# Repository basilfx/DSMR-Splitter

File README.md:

# DSMR Splitter
Active port expander for the P1 port on a Dutch Smart Meter (DSMR).

## Introduction
This is an active port expander for DSMR 5.0. Contrary to simple splitting
cables, this exapander buffers telegrams, and provides a dedicated port to
connected devices.

### Advantages
This design solves two (potential) issues compared to other splitters:

* Some port splitters have a primary and a secondary port. Only the primary
  port has the data-request line connected to the DSMR. This means that the
  secondary port cannot request telegrams on its own and depends on the device
  connected to the master port.
* A device connected to the secondary port could receive out-of-sync, if it
  depends on the data-request line. This could lead to incomplete/corrupt
  telegrams.

See [this](docs/Problem-statement.md) for more information.

## Features
* 3-port splitter.
* DSMR 5.0.
* No external power supply needed.

The splitter provides galvanic isolation between ports, if the 5 V is not used.
To read more on how this was achieved, see [this](docs/Isolation.md).

Furthemore, it requires a DSMR 5.0 meter because it provides 5 V power. Do note
that the power (5 V, 250 mA) provided by the DSMR has to be shared among all
readers, and the splitter itself requires ~50 mA.

Older DSMR versions can be supported by changing the firmware and providing 5 V
externally.

## Contents
* The `3d/` folder contains a 3D-printable design for an enclosure.
* The `firmware/` folder contains the RIOT-OS firmware used for the
  microcontroller.
* The `pcb/` folder contains the Kicad schema and board design.
* The `tools/` folder contains additional tools, such as a DSMR simulator.

## License
The work in this repository is covered by CC BY-NC-SA 4.0. See the `LICENSE.md`
file for more information.

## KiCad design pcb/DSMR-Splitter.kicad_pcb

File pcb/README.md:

# DSMR Splitter

## Features
* ARM Cortex M4 CPU with 1 MiB of flash and 256 KiB of RAM.
* 3 isolated output ports.
* Status LED.

## Board

## Schema
You can find the schema [here](DSMR-Splitter.pdf).

## BoM
The (interactive) BoM can be found [here](https://basilfx.github.io/DSMR-Splitter/pcb/BoM/ibom.html).

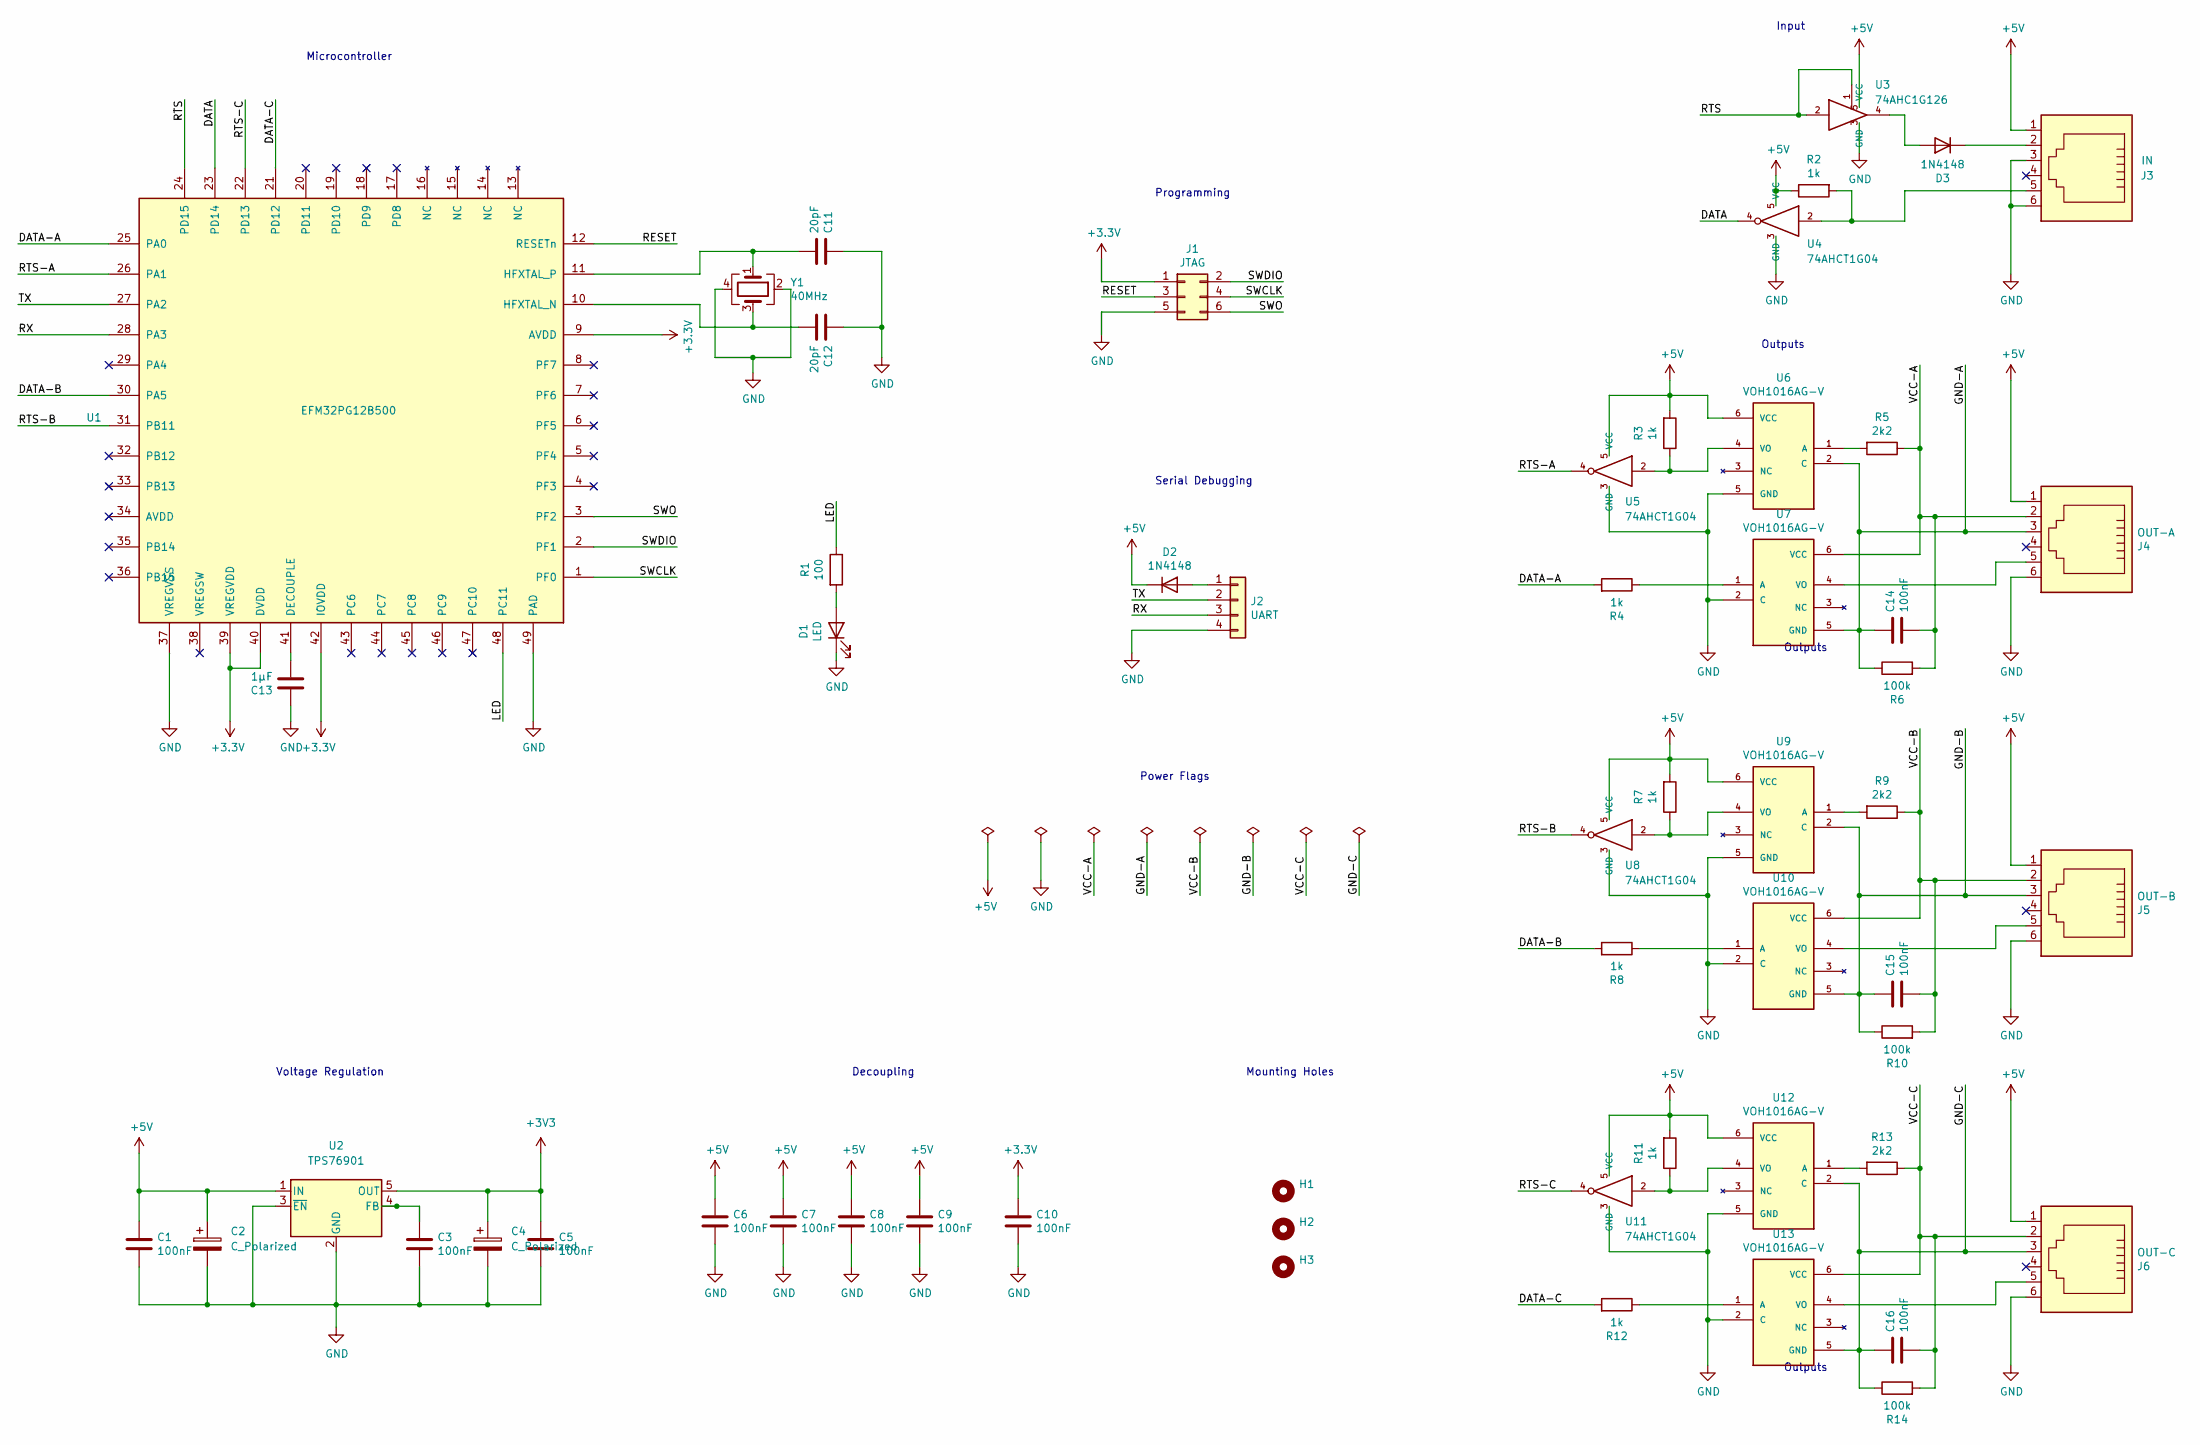
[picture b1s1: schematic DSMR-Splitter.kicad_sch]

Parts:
C1, C3, C5, C6, C7, C8, C9, C10, C14, C15, C16: 100nF; C_0603_1608Metric
C2, C4: C_Polarized; CP_EIA-3216-12_Kemet-S
C11, C12: 20pF; C_0603_1608Metric
C13: 1µF; C_0603_1608Metric
D1: LED; LED_0603_1608Metric
D2, D3: 1N4148; D_0603_1608Metric
H1, H2, H3: MountingHole; MountingHole_2.2mm_M2
J1: JTAG; PinHeader_2x03_P1.27mm_Vertical
J2: UART; PinHeader_1x04_P1.27mm_Vertical
J3: IN; RJ12_Amphenol_54601
J4: OUT-A; RJ12_Amphenol_54601
J5: OUT-B; RJ12_Amphenol_54601
J6: OUT-C; RJ12_Amphenol_54601
R1: 100; R_0603_1608Metric
R2, R3, R4, R7, R8, R11, R12: 1k; R_0603_1608Metric
R5, R9, R13: 2k2; R_0603_1608Metric
R6, R10, R14: 100k; R_0603_1608Metric
U1: EFM32PG12B500; QFN-48-1EP_7x7mm_P0.5mm_EP5.3x5.3mm
U2: TPS76901; SOT-23-5
U3: 74AHC1G126; SOT-23-5
U4, U5, U8, U11: 74AHCT1G04; SOT-23-5
U6, U7, U9, U10, U12, U13: VOH1016AG-V; SMDIP-6_W7.62mm; PARTREV 1.1
Y1: 40MHz; Crystal_SMD_2016-4Pin_2.0x1.6mm

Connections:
+5V: C1.1, C2.1, C6.1, C7.1, C8.1, C9.1, D2.1 (K), J3.1, J4.1, J5.1, J6.1, R2.1, R3.2, R7.2, R11.2, U2.1 (IN), U3.5 (VCC), U4.5 (VCC), U5.5 (VCC), U6.6 (VCC), U8.5 (VCC), U9.6 (VCC), U11.5 (VCC), U12.6 (VCC)
/DATA: U1.23 (PD14), U4.4
/DATA-A: R4.2, U1.25 (PA0)
/DATA-B: R8.2, U1.30 (PA5)
/DATA-C: R12.2, U1.21 (PD12)
/GND-A: C14.1, J4.3, R6.1, U6.2 (C), U7.5 (GND)
/GND-B: C15.1, J5.3, R10.1, U9.2 (C), U10.5 (GND)
/GND-C: C16.1, J6.3, R14.1, U12.2 (C), U13.5 (GND)
/LED: R1.1, U1.48 (PC11)
/RESET: J1.3, U1.12 (RESETn)
/RTS: U1.24 (PD15), U3.1, U3.2
/RTS-A: U1.26 (PA1), U5.4
/RTS-B: U1.31 (PB11), U8.4
/RTS-C: U1.22 (PD13), U11.4
/RX: J2.3, U1.28 (PA3)
/SWCLK: J1.4, U1.1 (PF0)
/SWDIO: J1.2, U1.2 (PF1)
/SWO: J1.6, U1.3 (PF2)
/TX: J2.2, U1.27 (PA2)
/VCC-A: C14.2, J4.2, R5.1, R6.2, U7.6 (VCC)
/VCC-B: C15.2, J5.2, R9.1, R10.2, U10.6 (VCC)
/VCC-C: C16.2, J6.2, R13.1, R14.2, U13.6 (VCC)
GND: C1.2, C2.2, C3.2, C4.2, C5.2, C6.2, C7.2, C8.2, C9.2, C10.2, C11.1, C12.1, C13.1, D1.1 (K), J1.5, J2.4, J3.3, J3.6, J4.6, J5.6, J6.6, U1.37 (VREGVSS), U1.49 (PAD), U2.2 (GND), U2.3 (~EN), U3.3 (GND), U4.3 (GND), U5.3 (GND), U6.5 (GND), U7.2 (C), U8.3 (GND), U9.5 (GND), U10.2 (C), U11.3 (GND), U12.5 (GND), U13.2 (C), Y1.2, Y1.4
unnamed: C3.1, U2.4 (FB)
unnamed: C11.2, U1.11 (HFXTAL_P), Y1.1
unnamed: C12.2, U1.10 (HFXTAL_N), Y1.3
unnamed: C13.2, U1.41 (DECOUPLE)
unnamed: D1.2 (A), R1.2
unnamed: D2.2 (A), J2.1
unnamed: D3.1 (K), J3.2
unnamed: D3.2 (A), U3.4
unnamed: J3.5, R2.2, U4.2
unnamed: J4.5, U7.4 (VO)
unnamed: J5.5, U10.4 (VO)
unnamed: J6.5, U13.4 (VO)
unnamed: R3.1, U5.2, U6.4 (VO)
unnamed: R4.1, U7.1 (A)
unnamed: R5.2, U6.1 (A)
unnamed: R7.1, U8.2, U9.4 (VO)
unnamed: R8.1, U10.1 (A)
unnamed: R9.2, U9.1 (A)
unnamed: R11.1, U11.2, U12.4 (VO)
unnamed: R12.1, U13.1 (A)
unnamed: R13.2, U12.1 (A)

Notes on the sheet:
Decoupling
Microcontroller
Outputs
Input
Serial Debugging
Mounting Holes
Voltage Regulation
Programming
Power Flags

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
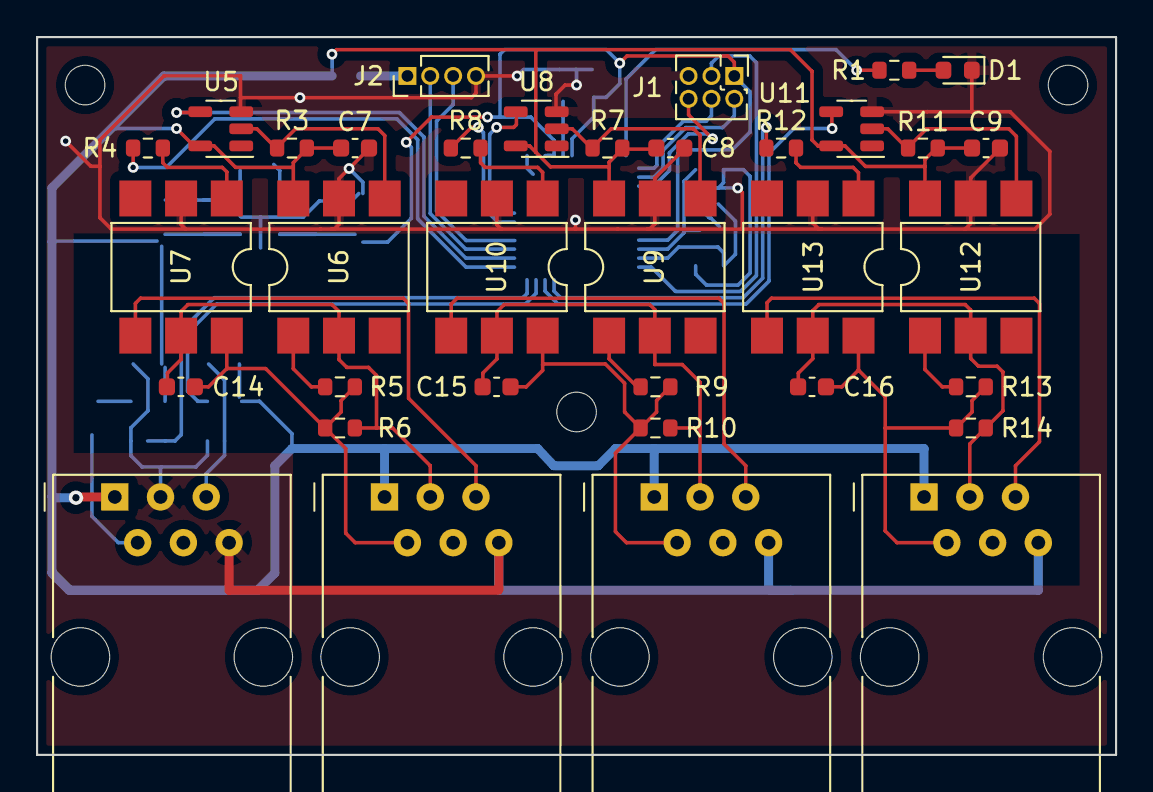
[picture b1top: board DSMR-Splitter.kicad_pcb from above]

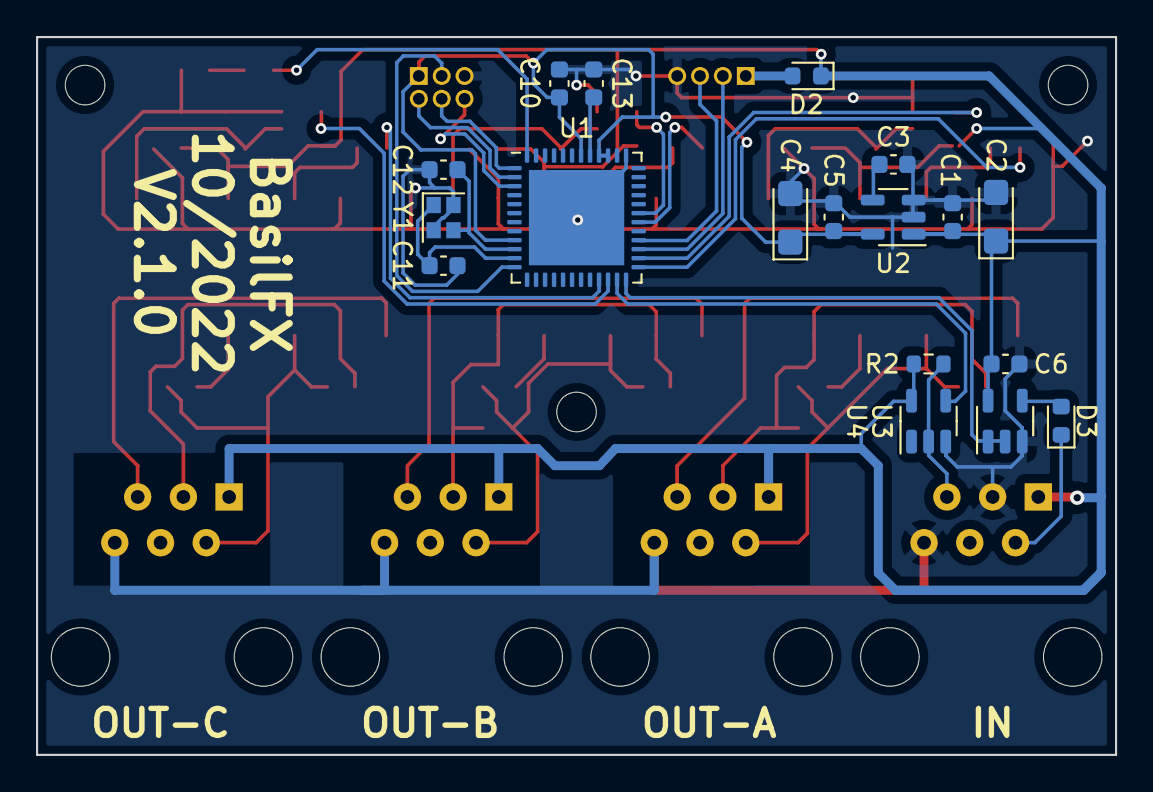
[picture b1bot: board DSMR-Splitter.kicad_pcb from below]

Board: 2 copper layers, 59.9 x 39.9 mm, 56 parts (18 on the bottom side), 45 nets.

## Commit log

2021-09-20 Initial commit.
2021-09-23 Typo fix
2022-03-14 Add board version 2.0.0
2022-03-14 Add firmware
2022-03-14 Add simulator
2022-03-14 Document firmware features
2022-07-27 Add bottom enclosure with arrows
2022-10-01 Adapt gitignore for KiCad6
2022-10-01 Upgrade project to KiCad 6.0
2022-10-04 Replace BoM with interactive BoM
2022-10-04 Add GitHub action to publish static content
2022-10-04 Annotate schema with order numbers
2022-10-04 Add Tracespace board render settings
2022-10-04 Replace 3D pictures with 2D pictures
